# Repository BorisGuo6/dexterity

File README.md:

# Project Dexterity

## Overview
Dexterity is a capstone project developed by ECE students at the University of Virginia (Class of 2025). The project consists of a robotic hand that can be controlled using a haptic feedback glove, providing a natural and intuitive way to control robotic movements while receiving tactile feedback. Three members of our team traveled to the Bay Area in December 2024 to showcase the project at the [Humanoids Summit](https://humanoidssummit.com/) in the Hugging Face booth (pictured above).

An summary of the project can be found in these [Figma slides](https://www.figma.com/deck/h1ZrgHnDu9oTQfUKUapgQW/Dexterity-Progress-Report?node-id=32-46&t=BGETurAAA480CFCk-1).

## Videos

The videos below showcase how the system's responsiveness and precision enable it to consistently catch balls.

https://github.com/user-attachments/assets/b5050c01-b495-40dd-bd65-899a9acaca80

https://github.com/user-attachments/assets/4d67e1bd-996e-49d0-b71a-232bf0a58b3a

## Project Structure
### [Firmware](firmware/)
- `HapticGlove/` - Firmware for the V2 control glove
- `RoboticArm/` - Firmware for the dexhand
- `PrototypeGlove/` - Firmware for the prototype control glove 
- `ESPNOW/` - ESP-NOW wireless communication implementations
- `test/` - Various test implementations and debugging tools

### [Hardware](hardware/)
- `cad/` - CAD files for 3D printing
  - `arm base/` - CAD files for the arm base and wire organization
  - `glove v2.4/` - CAD files for the latest interation of the V2 glove
  - `old/` - CAD files for the previous iterations of the V2 glove
- `pcb/`
  - `Forearm/` - PCB design files for the forearm
  - `Hand/` - PCB design files for the hand
  - `Library/` - KiCad library files
  - `gerber/` - Gerber files for manufacturing

### [Capstone](capstone/)
- `requirements/` - Project requirements and specifications from our capstone class 
- `reports/` - Project reports and presentations from our capstone class 

### [Media](media/)
- `images/` - Photos of the project and components
- `videos/` - Demo videos and presentations
- `diagrams/` - System diagrams and illustrations

## Features

### Robotic Arm
- Based on the open-source [Dexhand](https://www.dexhand.org/) project
  - Forearm shell and arm base were FDM printed using PETG filament
  - Everything else was resin printed using ABS-like resin, which provided smoother finishes and more accurate fits due to the higher resolution of SLA printing
- 16 degrees of freedom (DOF) across five fingers
  - 3 DOF per finger (flexion of PIP, flexion of MCP, abduction/adduction)
  - 4 DOF for thumb (extra degree for rotation)
  - Controlled by EMAX ES3352 digital servos
- 2 DOF in the wrist (pitch and yaw)
  - Controlled by Feetech SCS2332 serial servos 
  - These provide increased range of motion and torque in addition to having overcurrent protection
- Controlled by ESP32-S3 DevKitC-1 microcontroller
  - Housed on a Proto-PCB
  - ESP-NOW protocol for low-latency communication
- Force-sensitive resistors on each fingertip
  - 5kg maximum pressure sensing
  - These are wired up to a voltage divider circuit that connects to ADC channels on the ESP32
- System is powered by a 6V 10A power supply
  - Directly supplies power to servos
  - 3.3V regulation for control electronics
  - Wired through an amp meter for monitoring current draw

### Prototype Glove
- Original repository can be found here: [Prototype Finger Tracker](https://github.com/max-titov/finger-tracker)
- Hall effect sensor-based finger tracking
  - Each joint that was tracked had a rotating magnet and a hall effect sensor
  - 3 DOF per finger (flexion of PIP, flexion of MCP, abduction/adduction)
  - 4 DOF for thumb (extra degree for rotation)
  - Multiplexed sensor reading
- Controlled by a Xiao ESP32-C3 microcontroller
  - ESP-NOW protocol for low-latency communication
- Provided very accurate and responsive finger tracking

### V2 Control Glove
- Same hall effect sensor-based finger tracking as the prototype glove
  - 16 sensors total
  - Electrical complexity of the system introduced a lot of noise into the system, making the finger tracking less accurate than the prototype glove
- Dual PCB design
  - Hand PCB for sensors and haptics
  - Forearm PCB for processing and power
  - Connected with two ribbon cables
- Dual IMU system for wrist orientation
  - One IMU on hand PCB
  - One IMU on forearm PCB
  - Quaternion-based orientation calculation
- Haptic feedback system
  - Linear Resonant Actuators on each fingertip
  - I2C multiplexer for managing multiple LRA drivers
  - Variable intensity based on pressure sensing
- 3D printed design
  - Finger buckets housed LRA drivers and clamped onto fingers using rubber bands
  - Modular finger assemblies allowed easy swapping of parts during development
  - 2 straps per PCB housing attached the device to your hand
- Controlled by ESP32-S3 DevKitC-1 microcontroller
  - Housed on the Forearm PCB
  - ESP-NOW protocol for low-latency communication
- Control panel with LED indicators and mode switches
- Capable of running on battery power due to the onboard 3.3V regulator

## Getting Started
1. Good luck with building everything :)
2. Clone the repository
3. Install PlatformIO extension for VSCode
4. Open the desired project folder
5. Build and upload to your device

## Authors

- Max Titov 
  - Led the team by doing high level design of the whole system, assembled the robotic arm, designed the control gloves, and developed finger tracking/control libraries
  -   
- Alex Schaefer 
  - Architected the embedded software system, implemented ESP-NOW communication, and developed the high-level control structure using multi-threading
  -  
- Jackson Lamb 
  - Designed and tested the dual PCB system for the control glove and developed libraries for the control panel interfaces
  -  
- Jacob Hall 
  - Implemented the dual IMU system for wrist tracking, including quaternion mathematics and calibration routines
  -  
- Bhargav Moosani 
  - Designed and implemented the haptic feedback system using LRAs and force sensors, including wireless integration
  -  

## Acknowledgments
- [Original Dexhand Repository](https://github.com/TheRobotStudio/V1.0-Dexhand/) - Our robotic hand design is based on The Robot Studio's Dexhand project, licensed under CC BY-NC-SA 4.0.
- [Dexhand Website](https://www.dexhand.org/) - Trent Shumay from IoT Design Shop built two Dexhands and put together a website that compiled info about the project into a single page.
- [Prototype Finger Tracker](https://github.com/max-titov/finger-tracker) - My first glove that tracked 16 DOF of the fingers. This glove was used in a lot of the demonstrations of the teleop due to its better finger tracking capabilities.
- [Nepyope's Youtube](https://www.youtube.com/watch?v=iPtgvh6fNdQ) - The video of the first 16 DOF glove using hall effect sensors that inspired this whole project.
- [Nepyope's Project Homunculus](https://github.com/nepyope/Project-Homunculus) - The repository for the glove that inspired this project.

## License
This project is licensed under the MIT License - see the LICENSE file for details

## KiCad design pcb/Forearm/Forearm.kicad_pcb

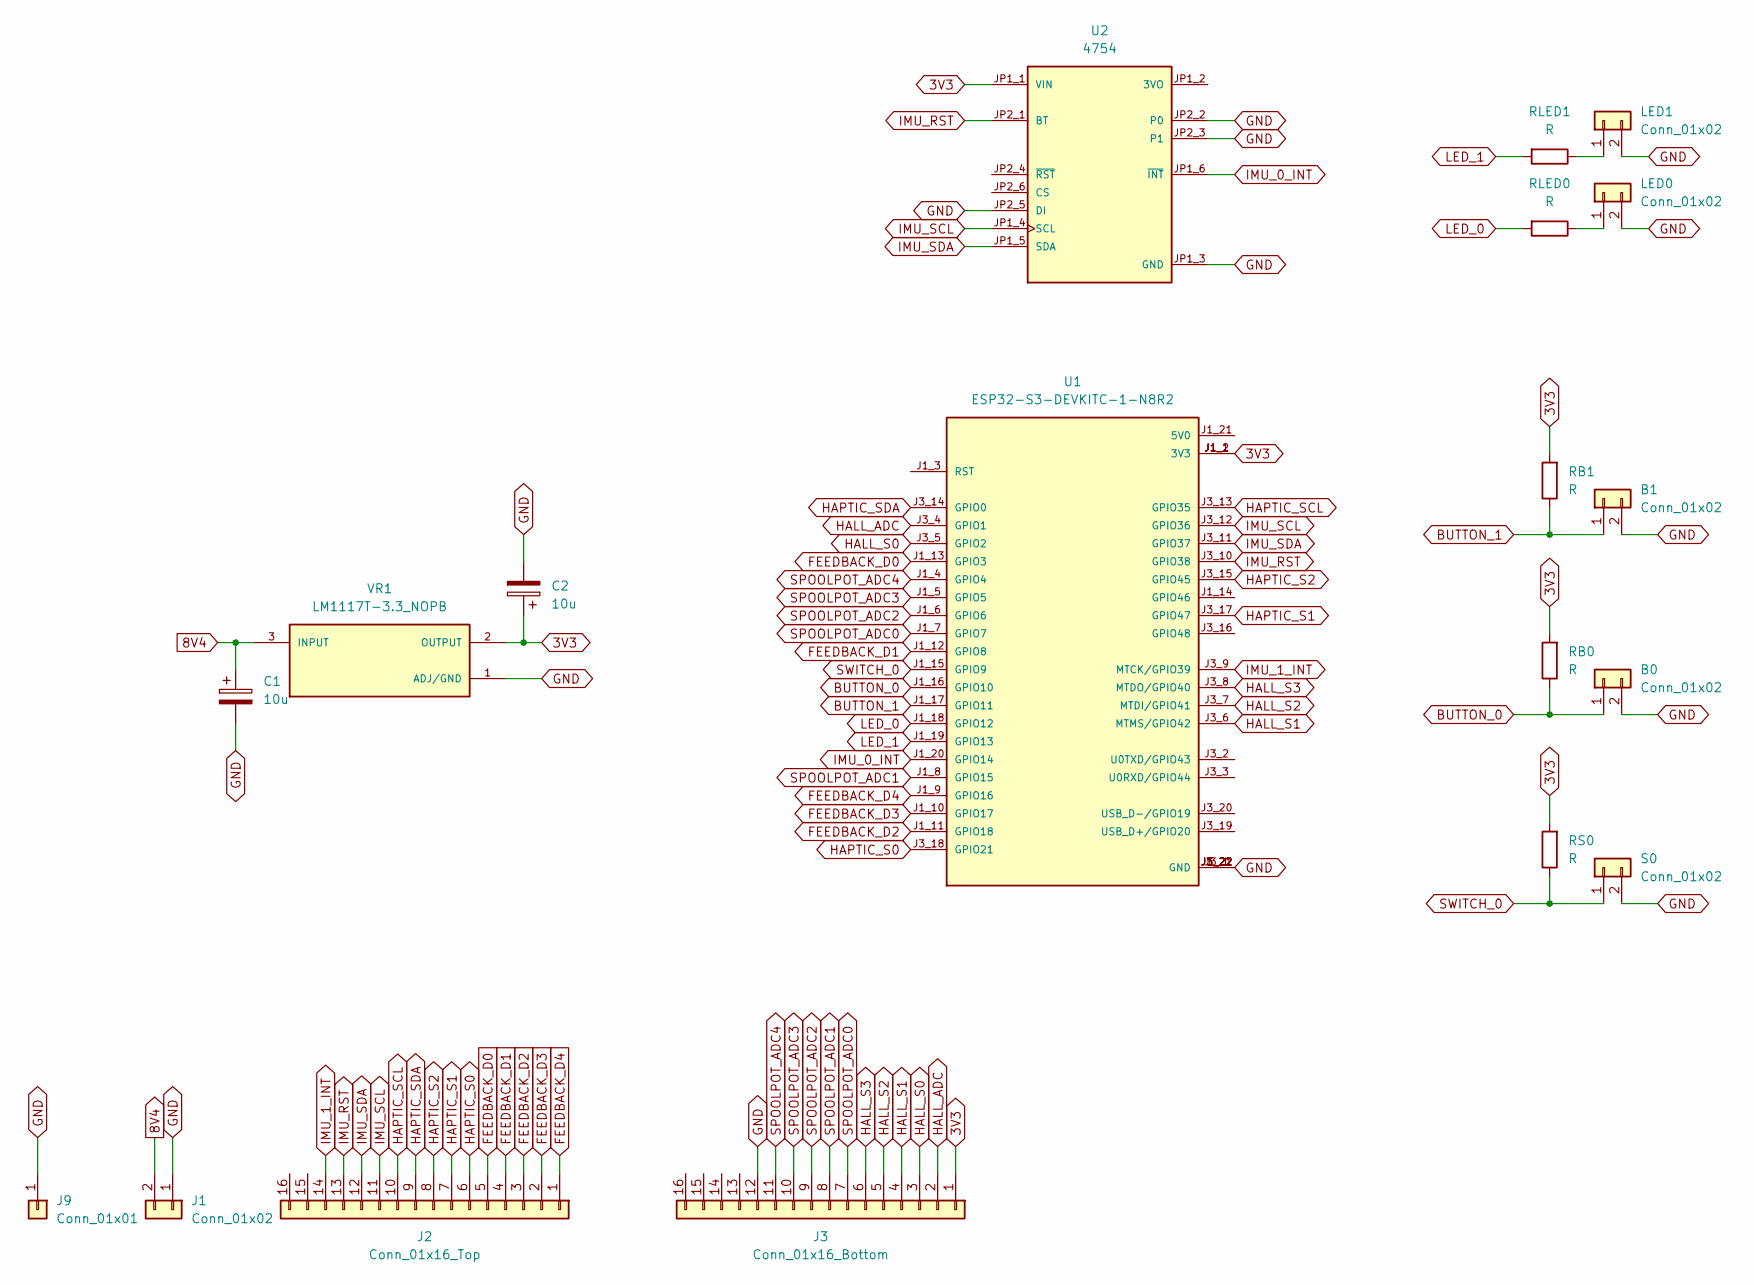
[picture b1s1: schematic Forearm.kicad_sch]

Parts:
B0, B1: Conn_01x02; PinSocket_1x02_P2.54mm_Vertical
C1, C2: 10u; C_1206_3216Metric
J1: Conn_01x02; PinSocket_1x02_P2.54mm_Vertical
J2: Conn_01x16_Top; CON_522071633_MOL
J3: Conn_01x16_Bottom; CON_522071633_MOL
J9: Conn_01x01; PinSocket_1x01_P2.54mm_Vertical
LED0, LED1: Conn_01x02; PinSocket_1x02_P2.54mm_Vertical
RB0, RB1: R; R_0402_1005Metric
RLED0, RLED1: R; R_0402_1005Metric
RS0: R; R_0402_1005Metric
S0: Conn_01x02; PinSocket_1x02_P2.54mm_Vertical
U1: ESP32-S3-DEVKITC-1-N8R2; XCVR_ESP32-S3-DEVKITC-1-N8R2; PARTREV V1
U2: 4754; MODULE_4754; PARTREV 2021-03-16
VR1: LM1117T-3.3_NOPB; PARTREV O

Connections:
3V3: C2.1, J3.1, RB0.2, RB1.2, RS0.2, U1.J1_1 (3V3), U1.J1_2 (3V3), U2.JP1_1 (VIN), VR1.2 (OUTPUT)
8V4: C1.1, J1.2, VR1.3 (INPUT)
BUTTON_0: B0.1, RB0.1, U1.J1_16 (GPIO10)
BUTTON_1: B1.1, RB1.1, U1.J1_17 (GPIO11)
FEEDBACK_D0: J2.5, U1.J1_13 (GPIO3)
FEEDBACK_D1: J2.4, U1.J1_12 (GPIO8)
FEEDBACK_D2: J2.3, U1.J1_11 (GPIO18)
FEEDBACK_D3: J2.2, U1.J1_10 (GPIO17)
FEEDBACK_D4: J2.1, U1.J1_9 (GPIO16)
GND: B0.2, B1.2, C1.2, C2.2, J1.1, J3.12, J9.1, LED0.2, LED1.2, S0.2, U1.J1_22 (GND), U1.J3_1 (GND), U1.J3_21 (GND), U1.J3_22 (GND), U2.JP1_3 (GND), U2.JP2_2 (P0), U2.JP2_3 (P1), U2.JP2_5 (DI), VR1.1 (ADJ/GND)
HALL_ADC: J3.2, U1.J3_4 (GPIO1)
HALL_S0: J3.3, U1.J3_5 (GPIO2)
HALL_S1: J3.4, U1.J3_6 (MTMS/GPIO42)
HALL_S2: J3.5, U1.J3_7 (MTDI/GPIO41)
HALL_S3: J3.6, U1.J3_8 (MTDO/GPIO40)
HAPTIC_S0: J2.6, U1.J3_18 (GPIO21)
HAPTIC_S1: J2.7, U1.J3_17 (GPIO47)
HAPTIC_S2: J2.8, U1.J3_15 (GPIO45)
HAPTIC_SCL: J2.10, U1.J3_13 (GPIO35)
HAPTIC_SDA: J2.9, U1.J3_14 (GPIO0)
IMU_0_INT: U1.J1_20 (GPIO14), U2.JP1_6 (~INT)
IMU_1_INT: J2.14, U1.J3_9 (MTCK/GPIO39)
IMU_RST: J2.13, U1.J3_10 (GPIO38), U2.JP2_1 (BT)
IMU_SCL: J2.11, U1.J3_12 (GPIO36), U2.JP1_4 (SCL)
IMU_SDA: J2.12, U1.J3_11 (GPIO37), U2.JP1_5 (SDA)
LED_0: RLED0.2, U1.J1_18 (GPIO12)
LED_1: RLED1.2, U1.J1_19 (GPIO13)
unnamed: LED0.1, RLED0.1
unnamed: LED1.1, RLED1.1
SPOOLPOT_ADC0: J3.7, U1.J1_7 (GPIO7)
SPOOLPOT_ADC1: J3.8, U1.J1_8 (GPIO15)
SPOOLPOT_ADC2: J3.9, U1.J1_6 (GPIO6)
SPOOLPOT_ADC3: J3.10, U1.J1_5 (GPIO5)
SPOOLPOT_ADC4: J3.11, U1.J1_4 (GPIO4)
SWITCH_0: RS0.1, S0.1, U1.J1_15 (GPIO9)

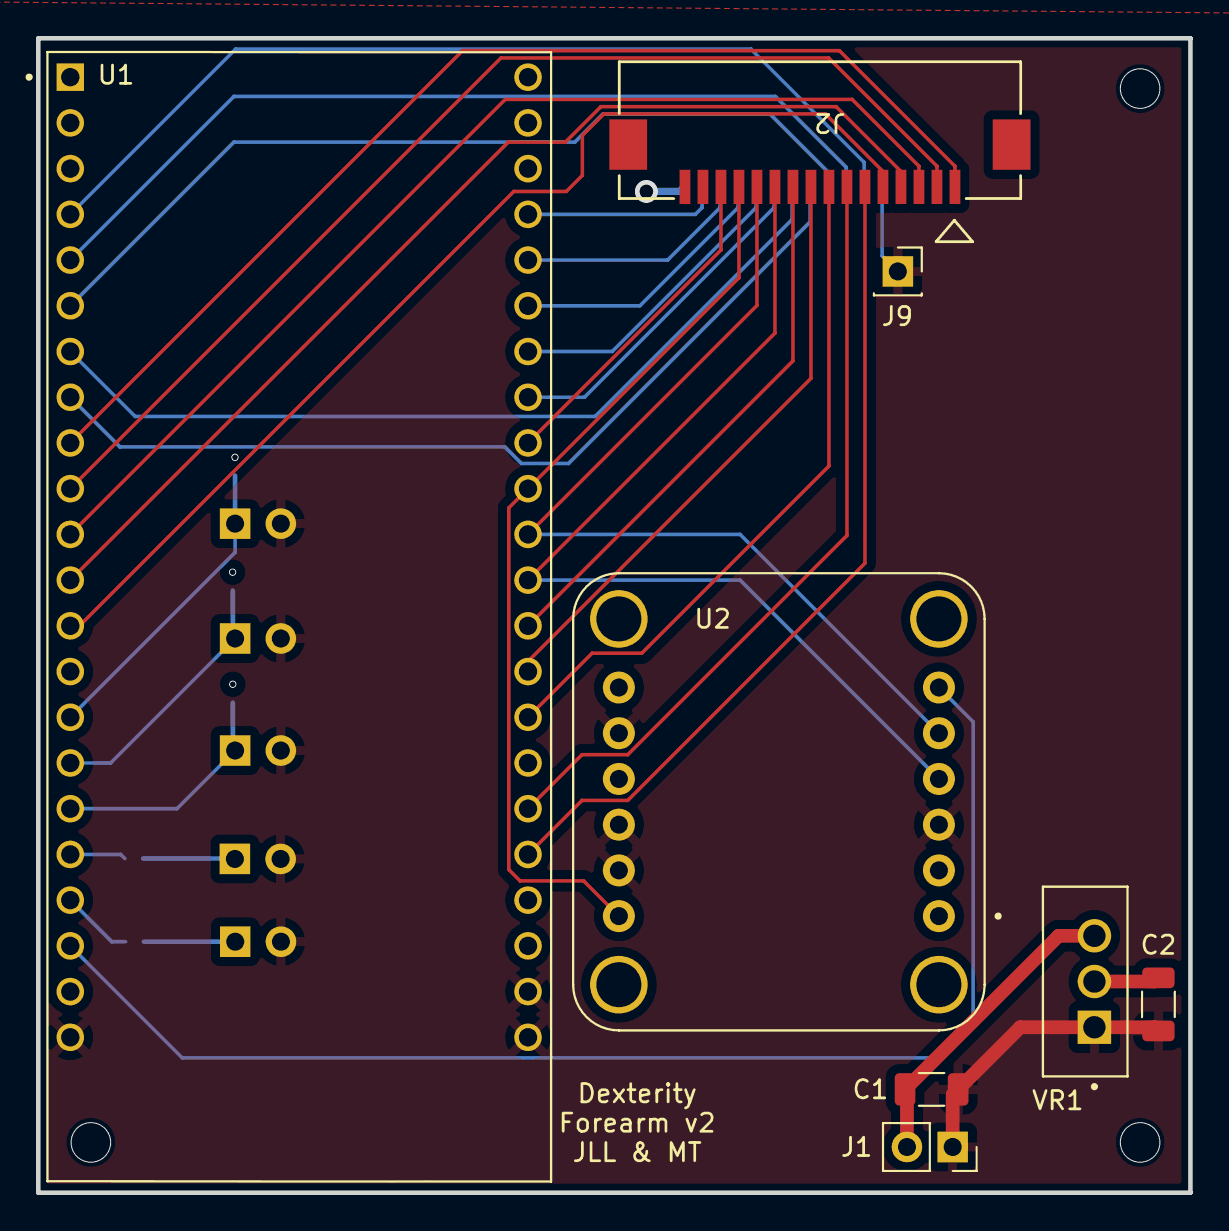
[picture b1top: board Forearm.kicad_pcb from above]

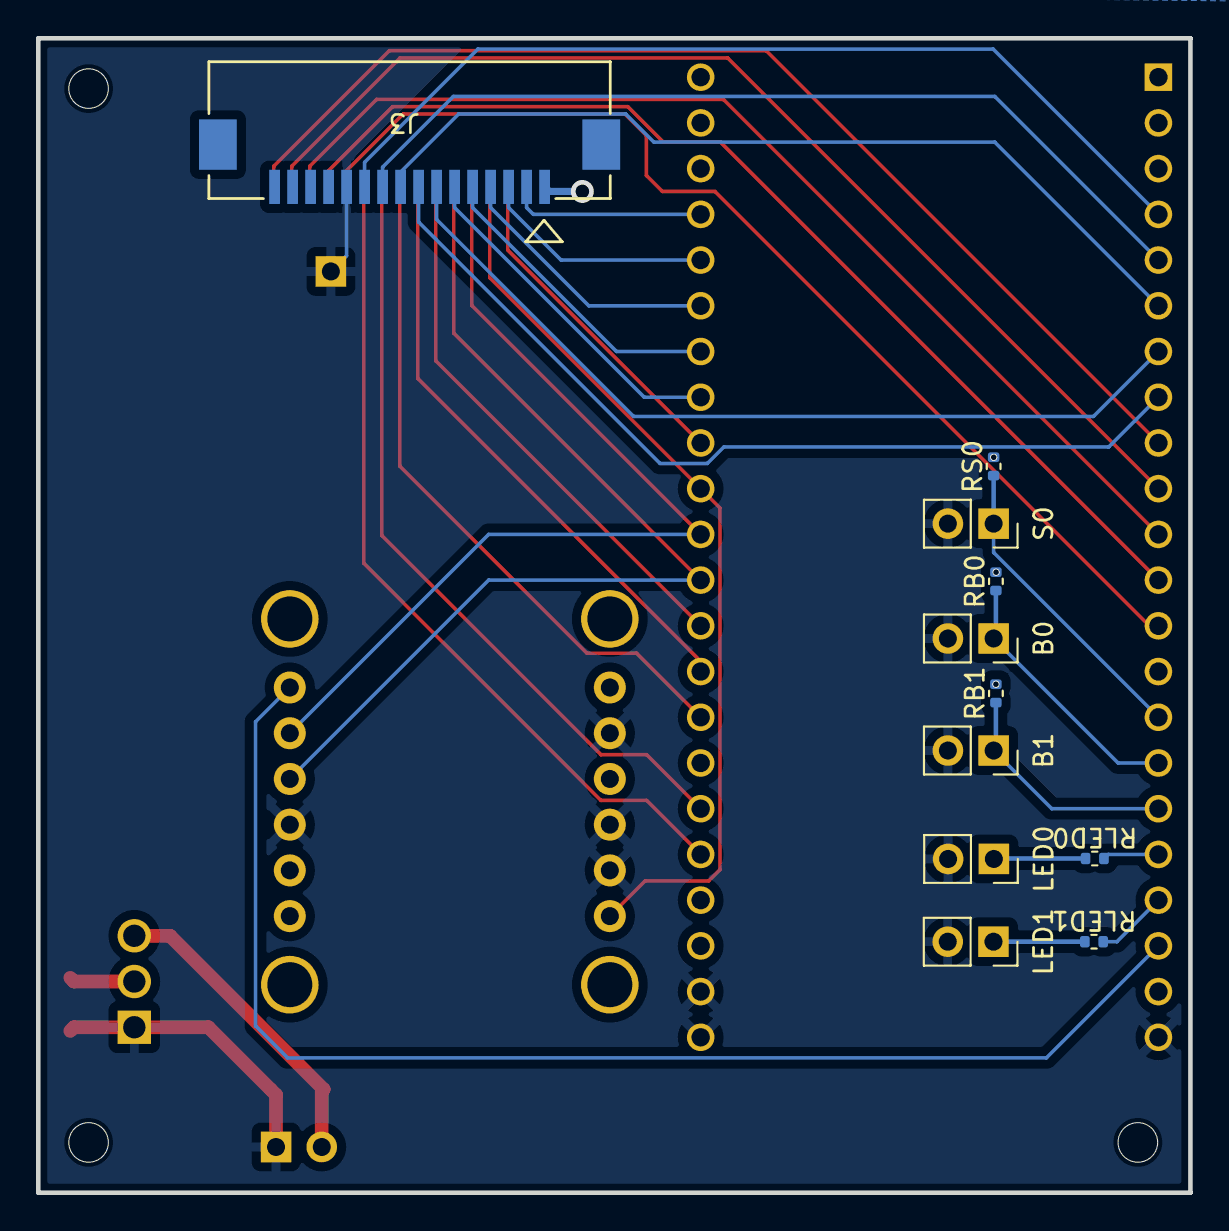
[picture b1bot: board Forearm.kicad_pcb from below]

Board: 4 copper layers, 64.0 x 64.1 mm, 19 parts (11 on the bottom side), 35 nets.

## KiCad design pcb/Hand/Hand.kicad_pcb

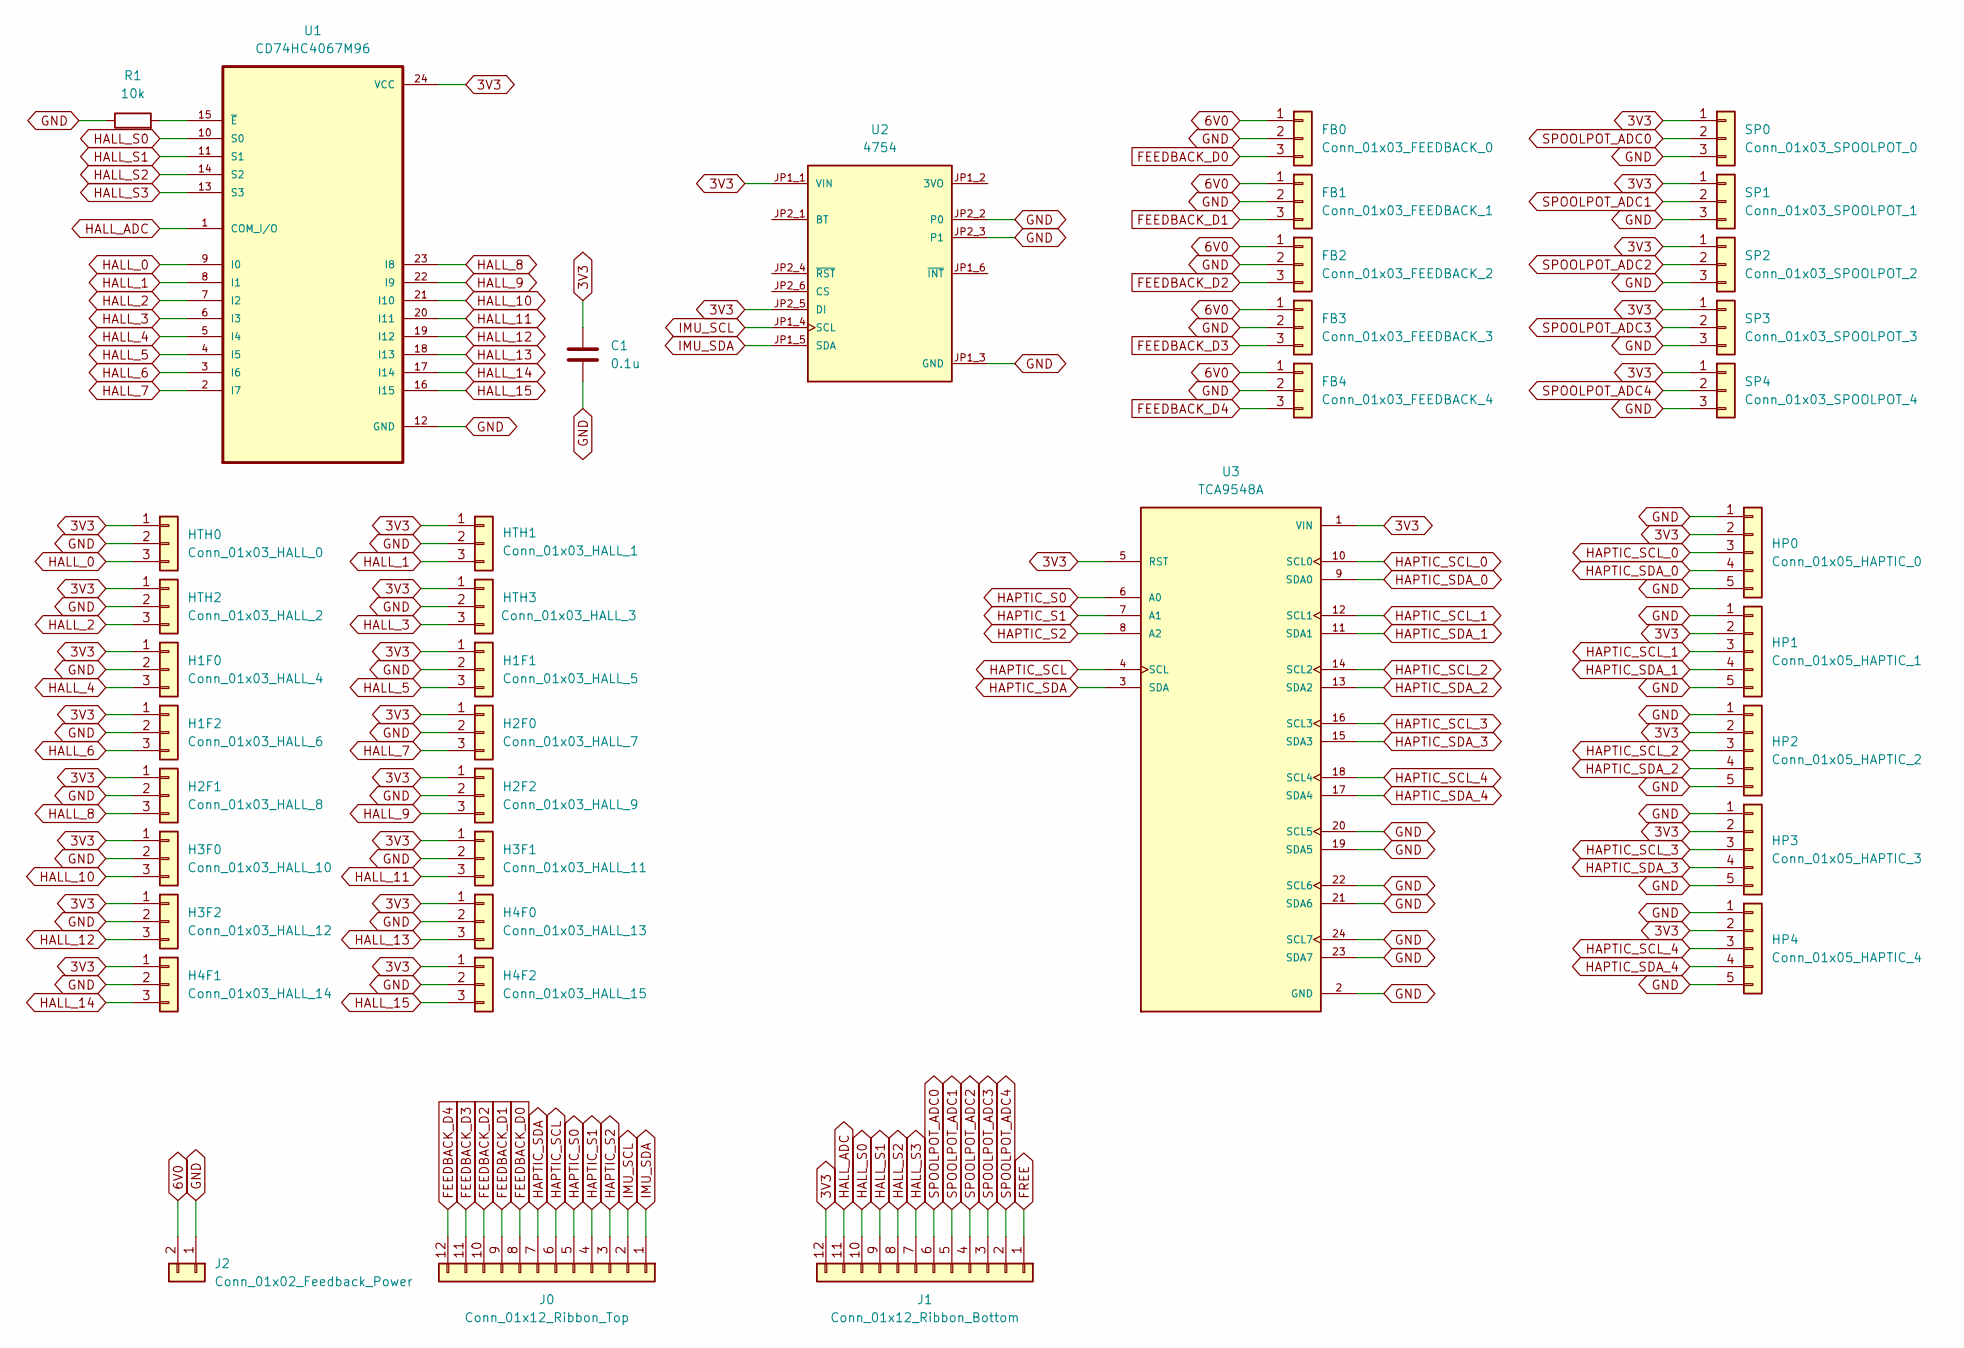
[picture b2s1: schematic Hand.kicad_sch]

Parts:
C1: 0.1u; C_1206_3216Metric
FB0: Conn_01x03_FEEDBACK_0; JST_SM03B-SRSS-TB_LF__SN_
FB1: Conn_01x03_FEEDBACK_1; JST_SM03B-SRSS-TB_LF__SN_
FB2: Conn_01x03_FEEDBACK_2; JST_SM03B-SRSS-TB_LF__SN_
FB3: Conn_01x03_FEEDBACK_3; JST_SM03B-SRSS-TB_LF__SN_
FB4: Conn_01x03_FEEDBACK_4; JST_SM03B-SRSS-TB_LF__SN_
H1F0: Conn_01x03_HALL_4; JST_SM03B-SRSS-TB_LF__SN_
H1F1: Conn_01x03_HALL_5; JST_SM03B-SRSS-TB_LF__SN_
H1F2: Conn_01x03_HALL_6; JST_SM03B-SRSS-TB_LF__SN_
H2F0: Conn_01x03_HALL_7; JST_SM03B-SRSS-TB_LF__SN_
H2F1: Conn_01x03_HALL_8; JST_SM03B-SRSS-TB_LF__SN_
H2F2: Conn_01x03_HALL_9; JST_SM03B-SRSS-TB_LF__SN_
H3F0: Conn_01x03_HALL_10; JST_SM03B-SRSS-TB_LF__SN_
H3F1: Conn_01x03_HALL_11; JST_SM03B-SRSS-TB_LF__SN_
H3F2: Conn_01x03_HALL_12; JST_SM03B-SRSS-TB_LF__SN_
H4F0: Conn_01x03_HALL_13; JST_SM03B-SRSS-TB_LF__SN_
H4F1: Conn_01x03_HALL_14; JST_SM03B-SRSS-TB_LF__SN_
H4F2: Conn_01x03_HALL_15; JST_SM03B-SRSS-TB_LF__SN_
HP0: Conn_01x05_HAPTIC_0; JST_SM05B-SRSS-TB_LF__SN_
HP1: Conn_01x05_HAPTIC_1; JST_SM05B-SRSS-TB_LF__SN_
HP2: Conn_01x05_HAPTIC_2; JST_SM05B-SRSS-TB_LF__SN_
HP3: Conn_01x05_HAPTIC_3; JST_SM05B-SRSS-TB_LF__SN_
HP4: Conn_01x05_HAPTIC_4; JST_SM05B-SRSS-TB_LF__SN_
HTH0: Conn_01x03_HALL_0; JST_SM03B-SRSS-TB_LF__SN_
HTH1: Conn_01x03_HALL_1; JST_SM03B-SRSS-TB_LF__SN_
HTH2: Conn_01x03_HALL_2; JST_SM03B-SRSS-TB_LF__SN_
HTH3: Conn_01x03_HALL_3; JST_SM03B-SRSS-TB_LF__SN_
J0: Conn_01x12_Ribbon_Top; 0522071233
J1: Conn_01x12_Ribbon_Bottom; 0522071233
J2: Conn_01x02_Feedback_Power; PinHeader_1x02_P2.54mm_Vertical
R1: 10k; R_0402_1005Metric
SP0: Conn_01x03_SPOOLPOT_0; JST_SM03B-SRSS-TB_LF__SN_
SP1: Conn_01x03_SPOOLPOT_1; JST_SM03B-SRSS-TB_LF__SN_
SP2: Conn_01x03_SPOOLPOT_2; JST_SM03B-SRSS-TB_LF__SN_
SP3: Conn_01x03_SPOOLPOT_3; JST_SM03B-SRSS-TB_LF__SN_
SP4: Conn_01x03_SPOOLPOT_4; JST_SM03B-SRSS-TB_LF__SN_
U1: CD74HC4067M96; SOIC127P1030X265-24N
U2: 4754; MODULE_4754; PARTREV 2021-03-16
U3: TCA9548A; MODULE_2717; PARTREV Sep 11, 2015

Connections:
3V3: C1.1, H1F0.1, H1F1.1, H1F2.1, H2F0.1, H2F1.1, H2F2.1, H3F0.1, H3F1.1, H3F2.1, H4F0.1, H4F1.1, H4F2.1, HP0.2, HP1.2, HP2.2, HP3.2, HP4.2, HTH0.1, HTH1.1, HTH2.1, HTH3.1, J1.12, SP0.1, SP1.1, SP2.1, SP3.1, SP4.1, U1.24 (VCC), U2.JP1_1 (VIN), U2.JP2_5 (DI), U3.1 (VIN), U3.5 (RST); also elsewhere on the board
6V0: FB0.1, FB1.1, FB2.1, FB3.1, FB4.1, J2.2
FEEDBACK_D0: FB0.3, J0.8; also elsewhere on the board
FEEDBACK_D1: FB1.3, J0.9; also elsewhere on the board
FEEDBACK_D2: FB2.3, J0.10; also elsewhere on the board
FEEDBACK_D3: FB3.3, J0.11; also elsewhere on the board
FEEDBACK_D4: FB4.3, J0.12; also elsewhere on the board
GND: C1.2, FB0.2, FB1.2, FB2.2, FB3.2, FB4.2, H1F0.2, H1F1.2, H1F2.2, H2F0.2, H2F1.2, H2F2.2, H3F0.2, H3F1.2, H3F2.2, H4F0.2, H4F1.2, H4F2.2, HP0.1, HP0.5, HP1.1, HP1.5, HP2.1, HP2.5, HP3.1, HP3.5, HP4.1, HP4.5, HTH0.2, HTH1.2, HTH2.2, HTH3.2, J2.1, R1.1, SP0.3, SP1.3, SP2.3, SP3.3, SP4.3, U1.12 (GND), U2.JP1_3 (GND), U2.JP2_2 (P0), U2.JP2_3 (P1), U3.2 (GND), U3.19 (SDA5), U3.20 (SCL5), U3.21 (SDA6), U3.22 (SCL6), U3.23 (SDA7), U3.24 (SCL7)
HALL_0: HTH0.3, U1.9 (I0)
HALL_1: HTH1.3, U1.8 (I1)
HALL_2: HTH2.3, U1.7 (I2)
HALL_3: HTH3.3, U1.6 (I3)
HALL_4: H1F0.3, U1.5 (I4)
HALL_5: H1F1.3, U1.4 (I5)
HALL_6: H1F2.3, U1.3 (I6)
HALL_7: H2F0.3, U1.2 (I7)
HALL_8: H2F1.3, U1.23 (I8)
HALL_9: H2F2.3, U1.22 (I9)
HALL_10: H3F0.3, U1.21 (I10)
HALL_11: H3F1.3, U1.20 (I11)
HALL_12: H3F2.3, U1.19 (I12)
HALL_13: H4F0.3, U1.18 (I13)
HALL_14: H4F1.3, U1.17 (I14)
HALL_15: H4F2.3, U1.16 (I15)
HALL_ADC: J1.11, U1.1 (COM_I/O); also elsewhere on the board
HALL_S0: J1.10, U1.10 (S0); also elsewhere on the board
HALL_S1: J1.9, U1.11 (S1); also elsewhere on the board
HALL_S2: J1.8, U1.14 (S2); also elsewhere on the board
HALL_S3: J1.7, U1.13 (S3); also elsewhere on the board
HAPTIC_S0: J0.5, U3.6 (A0); also elsewhere on the board
HAPTIC_S1: J0.4, U3.7 (A1); also elsewhere on the board
HAPTIC_S2: J0.3, U3.8 (A2); also elsewhere on the board
HAPTIC_SCL: J0.6, U3.4 (SCL); also elsewhere on the board
HAPTIC_SCL_0: HP0.3, U3.10 (SCL0)
HAPTIC_SCL_1: HP1.3, U3.12 (SCL1)
HAPTIC_SCL_2: HP2.3, U3.14 (SCL2)
HAPTIC_SCL_3: HP3.3, U3.16 (SCL3)
HAPTIC_SCL_4: HP4.3, U3.18 (SCL4)
HAPTIC_SDA: J0.7, U3.3 (SDA); also elsewhere on the board
HAPTIC_SDA_0: HP0.4, U3.9 (SDA0)
HAPTIC_SDA_1: HP1.4, U3.11 (SDA1)
HAPTIC_SDA_2: HP2.4, U3.13 (SDA2)
HAPTIC_SDA_3: HP3.4, U3.15 (SDA3)
HAPTIC_SDA_4: HP4.4, U3.17 (SDA4)
IMU_1_INT: U2.JP1_6 (~INT); also elsewhere on the board
IMU_1_RST: U2.JP2_4 (~RST); also elsewhere on the board
IMU_SCL: J0.2, U2.JP1_4 (SCL); also elsewhere on the board
IMU_SDA: J0.1, U2.JP1_5 (SDA); also elsewhere on the board
unnamed: R1.2, U1.15 (~E)
SPOOLPOT_ADC0: J1.6, SP0.2; also elsewhere on the board
SPOOLPOT_ADC1: J1.5, SP1.2; also elsewhere on the board
SPOOLPOT_ADC2: J1.4, SP2.2; also elsewhere on the board
SPOOLPOT_ADC3: J1.3, SP3.2; also elsewhere on the board
SPOOLPOT_ADC4: J1.2, SP4.2; also elsewhere on the board

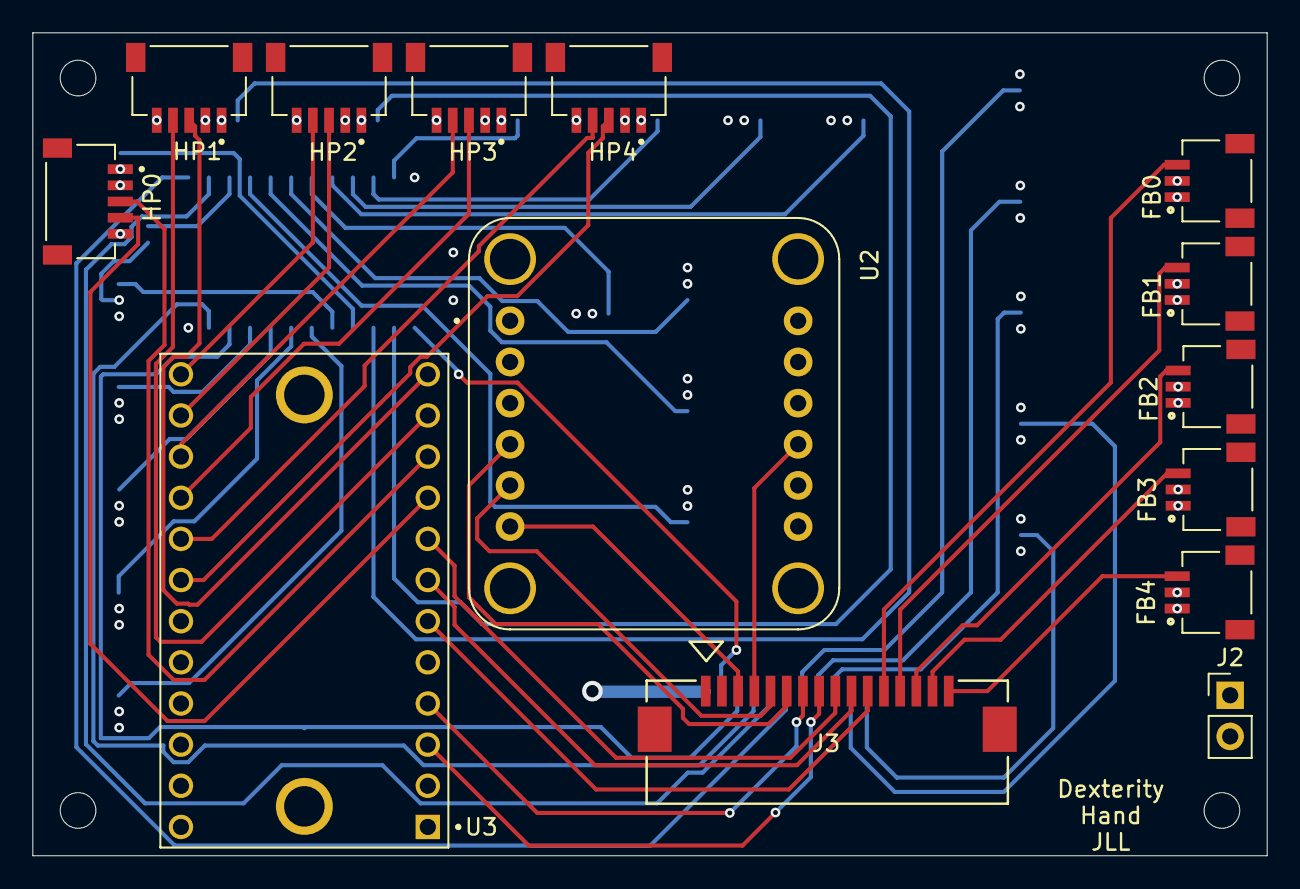
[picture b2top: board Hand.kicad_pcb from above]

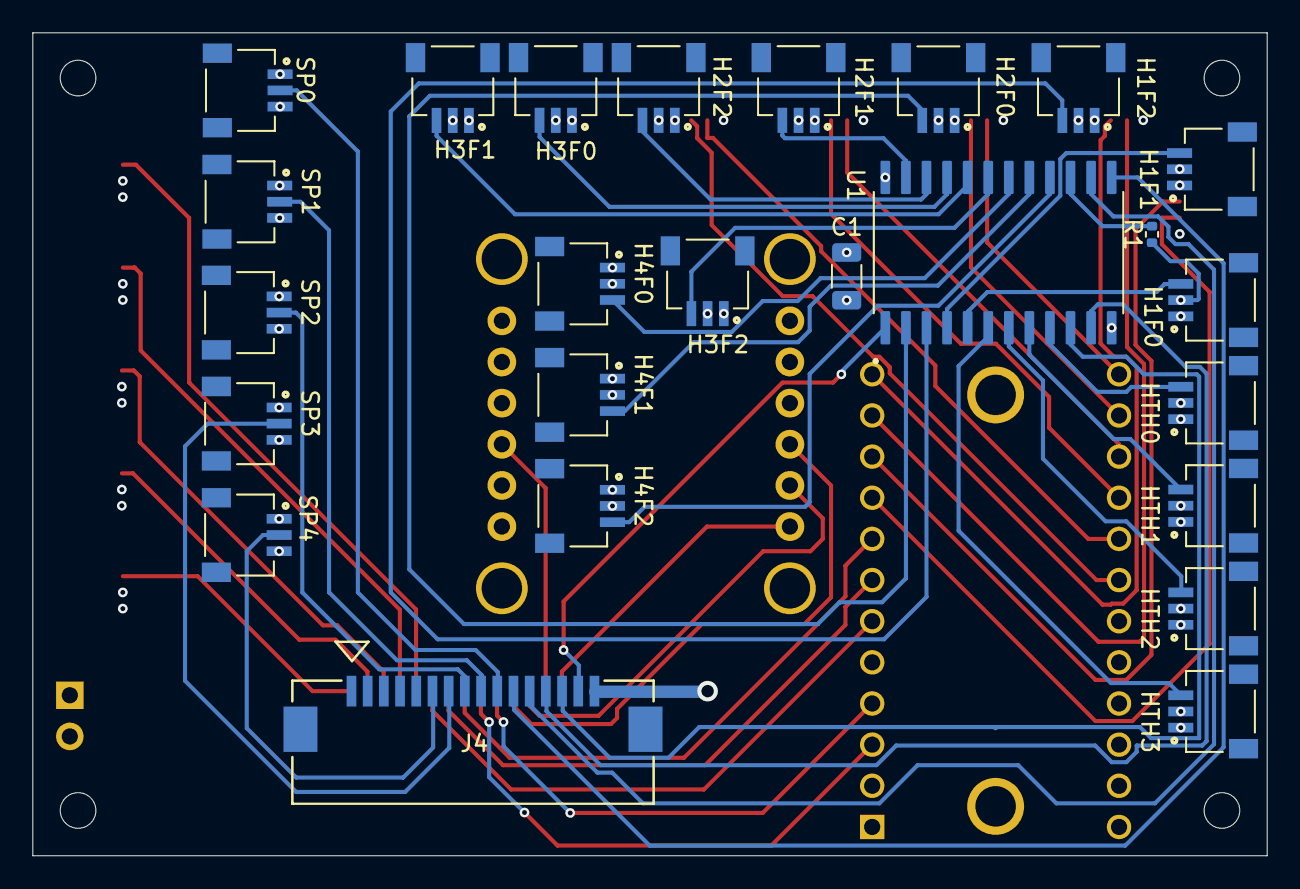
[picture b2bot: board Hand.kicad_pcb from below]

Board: 4 copper layers, 76.2 x 50.8 mm, 39 parts (25 on the bottom side), 54 nets.

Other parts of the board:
J3: Conn_01x16_Top; CON_522071633_MOL
J4: Conn_01x16_Bottom; CON_522071633_MOL

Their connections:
3V3: J4.16; also elsewhere on the board
FEEDBACK_D0: J3.12; also elsewhere on the board
FEEDBACK_D1: J3.13; also elsewhere on the board
FEEDBACK_D2: J3.14; also elsewhere on the board
FEEDBACK_D3: J3.15; also elsewhere on the board
FEEDBACK_D4: J3.16; also elsewhere on the board
HALL_ADC: J4.15; also elsewhere on the board
HALL_S0: J4.14; also elsewhere on the board
HALL_S1: J4.13; also elsewhere on the board
HALL_S2: J4.12; also elsewhere on the board
HALL_S3: J4.11; also elsewhere on the board
HAPTIC_S0: J3.11; also elsewhere on the board
HAPTIC_S1: J3.10; also elsewhere on the board
HAPTIC_S2: J3.9; also elsewhere on the board
HAPTIC_SCL: J3.7; also elsewhere on the board
HAPTIC_SDA: J3.8; also elsewhere on the board
IMU_1_INT: J3.3; also elsewhere on the board
IMU_1_RST: J3.4; also elsewhere on the board
IMU_SCL: J3.6; also elsewhere on the board
IMU_SDA: J3.5; also elsewhere on the board
SPOOLPOT_ADC0: J4.10; also elsewhere on the board
SPOOLPOT_ADC1: J4.9; also elsewhere on the board
SPOOLPOT_ADC2: J4.8; also elsewhere on the board
SPOOLPOT_ADC3: J4.7; also elsewhere on the board
SPOOLPOT_ADC4: J4.6; also elsewhere on the board

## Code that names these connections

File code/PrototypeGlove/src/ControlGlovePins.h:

// file to define pins on ESP32 board

// left side pins
#define SPOOL_POT_ADC0 4        // 4
#define SPOOL_POT_ADC1 5        // 5
#define SPOOL_POT_ADC2 6        // 6
#define SPOOL_POT_ADC3 7        // 7
#define SPOOL_POT_ADC4 15       // 15
#define FEEDBACK_SERVO_D4 16    // 16
#define FEEDBACK_SERVO_D3 17    // 17
#define FEEDBACK_SERVO_D2 18    // 18
#define FEEDBACK_SERVO_D1 8     // 8
#define FEEDBACK_SERVO_D0 3     // 3
// pin 46 unused                // 46
#define SWITCH_0 9              // 9
#define BUTTON_0 10             // 10
#define BUTTON_1 11             // 11
#define LED_0 12                // 12
#define LED_1 13                // 13
#define IMU_INT_0 14            // 14

// right side pins
#define U0_TX 43                // TX
#define U0_RX 44                // RX
#define HALL_ADC 1              // 1
#define HALL_S0 2               // 2
#define HALL_S1 42              // 42
#define HALL_S2 41              // 41
#define HALL_S3 40              // 40
#define IMU_INT_1 39            // 39
#define IMU_RST 38              // 38
#define IMU_SDA 37              // 37
#define IMU_SCL 36              // 36
#define HAPTIC_SCL 35           // 35
#define HAPTIC_SDA 0            // 0
#define HAPTIC_S2 45            // 45
#define INTERNAL_RGB_LED 48     // 48
#define HAPTIC_S1 47            // 47
#define HAPTIC_S0 21            // 21
#define USB_D_PLUS 20           // 20
#define USB_D_MINUS 19          // 19

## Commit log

2024-09-10 set up readme
2024-10-03 created code file structure and added haptic arduinio code
2024-10-03 added IMU example
2024-10-03 moved imu coms arduino code to a folder
2024-10-09 rough first version of pcbs
2024-10-09 added symbol and footprint files
2024-10-10 draft schematic for MDR
2024-10-13 replaced KiCad project zip files w/ raw project files
2024-10-16 added servo code
2024-10-16 forward annotated schms to pcbs, added gnd and pwr planes, begun part placement
2024-10-17 completed tentative part layout
2024-10-20 updated and routed hand pcb
2024-10-20 testing servo limits
2024-10-21 revised hand and made pass at routing forearm pcb
2024-10-21 Create ESPNOW folder in code
2024-10-21 uploading code for ESPNOW communication
2024-10-21 fixed arduino folders
2024-10-21 re-did layout of forearm board
2024-10-22 merging jackson pcb into main
2024-10-22 updates 10/21, reliability testing
2024-10-22 re-routed forearm board w/o switches etc
2024-10-23 Parameterized and rearranged code for simple external use
2024-10-23 Update to represent correct finger pos vals
2024-10-23 revised pcbs in preparation for pcb review; added pull-ups etc to forearm
2024-10-23 added gitignore
2024-10-23 re-work of pcbs for pin issues in progress 1
2024-10-24 added DevKitC_Test platformio project that has the debugger set up
2024-10-24 remove dummy text file
2024-10-24 created haptictest project for bhargav
2024-10-25 modified ESPNOW code in platform.io to reflect library differences
2024-10-25 separated ESPNOW code into importable libraries
2024-10-25 revised pcbs in prep for manufacture, rev2
2024-10-25 pcbs for order, rev3
2024-10-25 hand boatd final?
2024-10-25 actually final pcbs
2024-10-25 updated symbols & footprints
2024-10-25 added ground pours and generated gerbers for pcbs
2024-10-27 updated arduinio sketch to work with both servos
2024-10-27 added second servo to arduino sketch
2024-10-27 added IMU Test platform io directory
2024-10-27 updated IMUTest pio config
2024-10-27 added baseline 2 IMU code
2024-10-28 one finger working with flexion and abduction of the MCP joint
2024-10-29 updating interface for ESPNOW libraries
2024-10-29 updated .gitignore and untracked .DS_Store files
2024-10-29 added quat to euler conversion
2024-10-30 added comp flag turning off/on teleplot output data format
2024-10-30 added IMU report request compilation flags
2024-10-30 added get_bno_addr IMU function
2024-10-31 moved prototype glove code to this repo and started working on calibration
2024-11-03 calibration working for mcp flexion and abduction in PrototypeGlove project
2024-11-03 OneFingerTest working with calibrated data from glove
2024-11-04 used new version of alex's ESPNOW library and removed delays and waits in the library for quicker startup
2024-11-04 created library files and wrote setup function
2024-11-04 finger control library working with index finger
2024-11-04 sample multithreading
2024-11-04 two fingers moving
2024-11-04 four fingers moving
2024-11-04 created dev branch
2024-11-10 firstpass at re-factoring Hall effect sensor code into library
2024-11-10 polished Hall effect sensor library; added docstrings for public interface
2024-11-12 added library files and updated forearm schematic
2024-11-12 edited esp32 footprint
2024-11-13 updated esp32 pins on schematic
2024-11-13 board done will upload to JCL to check for errors
2024-11-13 forearm ready to be manufactured
2024-11-13 created test project to see if hand PCB hall effect sensors work
2024-11-13 send PCB off to JLC and cleaned up folders
2024-11-14 tested orginal 8 motor functionatlity with the more complete hand
2024-11-17 found out that esp32s3 only has 8 pwn channels, gonna start working on using a separate 16 channel PWN board
2024-11-17 got pwm board working in PWM_BoardTest
2024-11-17 started new lib for the pwm board
2024-11-18 updated haptic driver for I2C on ESP32
2024-11-18 comment edits
2024-11-18 outline code for haptic glove
2024-11-18 pwm board library working with 12 servos
2024-11-19 added header file for esp32 pins
2024-11-20 fixed bug that caused tip movment to be controlled by mcp flexion
2024-11-20 thumb moving, not very well yet tho
2024-11-21 thumb sorta working
2024-11-24 Added GloveControlPanel library and test project
2024-11-25 started itegrating hall effect lib by cleaning up syntax errors
2024-11-25 added ISR tes project
2024-11-25 code running but not working
2024-11-25 hall effect sensors library working in HallEffectLibTest
2024-11-25 updated testing code for glove control panel
2024-11-25 working on separating hall effect sensor library into finger tracking library
2024-11-26 HallEffectSensor and FingerTracking library work with prototype glove
2024-11-26 libraries work but are noisier than Prototype Glove code for some reason...
2024-11-26 added hand control panel and hand pins header file
2024-11-26 updated esp32_multithreading to be timer ISR friendly
2024-11-26 made v1 of finger attachment mechanism
2024-11-26 updated interface for read and set methods
2024-11-26 high level integration of robotic arm code
2024-11-26 updated haptic library; created driver for LRA/FSR test
2024-11-26 finger tracking lib is creating less noisy data now
2024-11-27 RoboticArm works with ESP32 swapped board
2024-11-27 updated ESPNOW libs
2024-11-27 arm control lib working from the bottom up
2024-11-27 updated RoboticArm and HapticGlove projects. Fixed Guru Errors
2024-11-27 cleaned up FingerTracking, EmaxServoControl, and ArmControl and added servo position printing
2024-11-27 caught haptic glove up to robotic arm
2024-11-27 fixed thumb movement on control glove side
2024-11-27 fixed ISR numbers
2024-11-27 full robotic arm itegration
2024-11-30 created v2 of finger upper and lower
2024-11-30 edit updated angle measurement lines
2024-11-30 almost done with arm and joint mechanism
2024-11-30 added IMU library in IMU_debugging
2024-12-01 changed wrist data to uint32
2024-12-01 adjusted wrist pos data size in robotic arm
2024-12-01 v2.2 of control glove finger tracker
2024-12-01 added IMU code
2024-12-01 made some fixes
2024-12-01 added test project for draft of HapticFeedback library
2024-12-01 trying again: draft of HapticFeedback library
2024-12-01 integrated SCServo code to Robotic Arm
2024-12-01 added tentative support for i2c mux to HapticFeedback
2024-12-02 working on v2.4
2024-12-03 updated LRA/FSR test pins
2024-12-03 added define to remove blocking if IMUs disconnected
2024-12-04 grounded a0-a2 pins of i2c mux in setupFeedback method
2024-12-04 added drivers for wireless haptic test
2024-12-04 added initialization for each LRA
2024-12-04 integrated pressure sensors and haptic code
2024-12-04 mux test added to wireless haptic driver
2024-12-04 forearm enclosure
2024-12-05 mux select method updated
2024-12-07 glove v2 finger tracking project
2024-12-07 attempt 1 integrating hall effect v2
2024-12-08 reverted to code from 12-2, integrated hall effect v2
2024-12-08 added method for measuring rate of callback completion
2024-12-08 polished timing
2024-12-08 brought libs back up to date
2024-12-08 added ISR tracking to Robotic Arm
2024-12-08 integrated buzzer code, updated ESPNOW
2024-12-09 integration for glove control panel, pressure sensors in robotic arm
2024-12-09 added updated wrist control code
2024-12-09 (semi) updated robotic arm pins
2024-12-09 updated pins robotic arm
2024-12-09 added filter to hall effect sensors
2024-12-09 fixed error in hall effect filter
2024-12-09 control glove updates
2024-12-10 Post demo push
2024-12-10 changes during demo day to robotic arm and halleffectlibtest
2024-12-11 int LED: initialization -- blue -> controlPanel -> (ifIMU red -> initIMU -> pink -> checknonzero -> purple -> wait for button ->) orange -> finger tracking -> off . . . calibration green until done
2024-12-11 draft of moving average filter code for finger position readings
2024-12-11 changed position of control panel initialize in main
2024-12-11 color changes
2024-12-11 ESPNOW adjustments
2024-12-11 wifi data not sending to hand
2024-12-11 save
2024-12-11 fixed ESPNOW issues
2024-12-11 more debugging with git
2024-12-11 resolved pressuresensors conflict
2024-12-11 added updating to finger position data after first averaging
2024-12-26 reorganization of project and started working on readmes
2024-12-26 reorganizing CAD files
2024-12-26 updated license
2024-12-26 further reorganizing cad files
2024-12-26 added forearm enclosure and thumb attachment stls
2024-12-28 more organization
2024-12-29 restructure project and working on the main readme
2024-12-29 working on firmware readme
2024-12-30 adding images to readmes
2024-12-30 fixed some images
2024-12-30 change image sizes
2025-01-01 Update README.md with videos
2025-01-02 added more photos and videos and a readme for the capstone folder
2025-01-02 small readme changes
2025-01-02 capstone readme update
2025-02-04 updated license to MIT
